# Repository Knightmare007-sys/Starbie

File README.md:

# Starbie
A tiny motion control digital pet

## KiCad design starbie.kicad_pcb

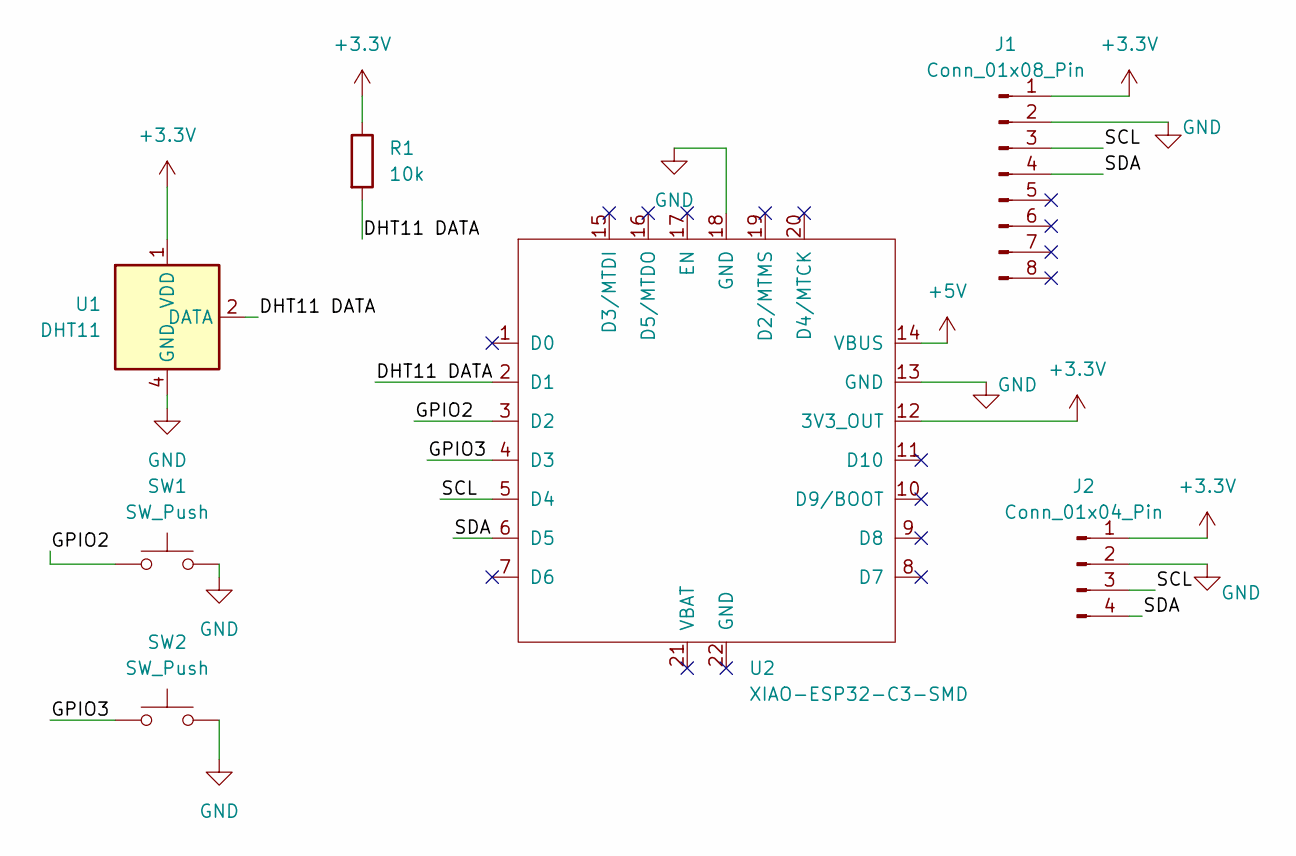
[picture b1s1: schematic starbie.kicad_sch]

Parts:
J1: Conn_01x08_Pin; PinHeader_1x08_P2.54mm_Vertical
J2: Conn_01x04_Pin; Display_128x64_096_I2C
R1: 10k; R_Axial_DIN0204_L3.6mm_D1.6mm_P7.62mm_Horizontal
SW1, SW2: SW_Push; SW_Cherry_MX_1.00u_PCB
U1: DHT11; Aosong_DHT11_5.5x12.0_P2.54mm
U2: XIAO-ESP32-C3-SMD

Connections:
+3.3V: J1.1, J2.1, R1.1, U1.1 (VDD), U2.12 (3V3_OUT)
+5V: U2.14 (VBUS)
/DHT11 DATA: R1.2, U1.2 (DATA), U2.2 (D1)
/GPIO2: SW1.1, U2.3 (D2)
/GPIO3: SW2.1, U2.4 (D3)
/SCL: J1.3, J2.3, U2.5 (D4)
/SDA: J1.4, J2.4, U2.6 (D5)
GND: J1.2, J2.2, SW1.2, SW2.2, U1.4 (GND), U2.13 (GND), U2.18 (GND)

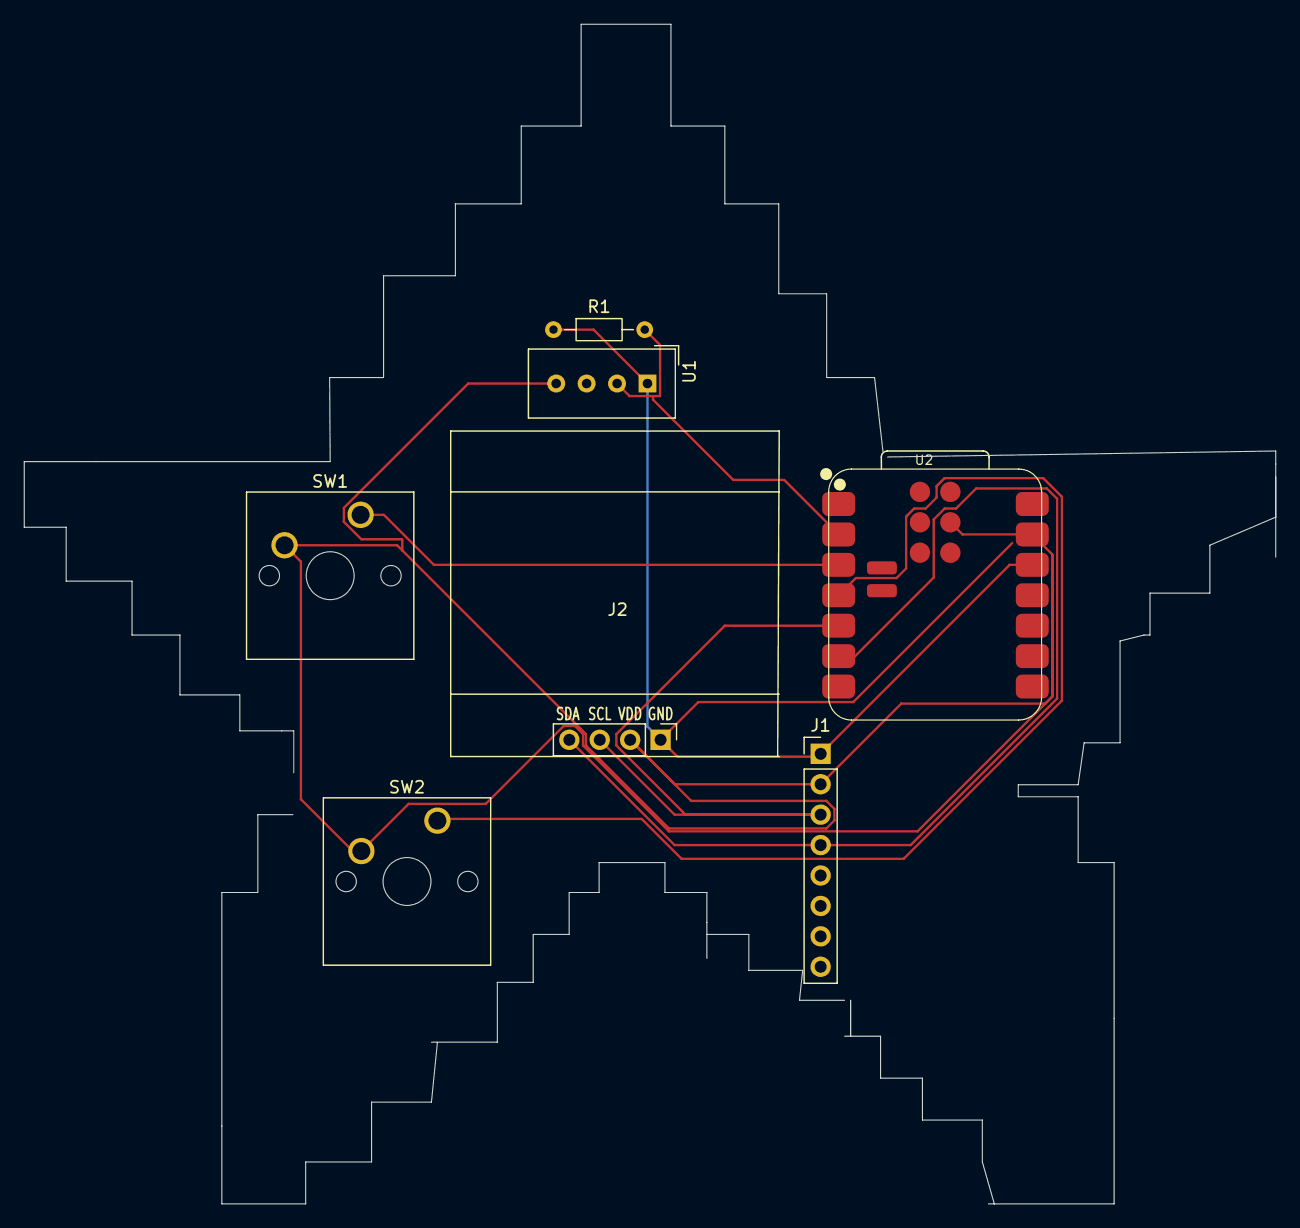
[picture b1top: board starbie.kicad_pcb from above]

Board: 2 copper layers, 104.5 x 98.5 mm, 7 parts (0 on the bottom side), 7 nets.
